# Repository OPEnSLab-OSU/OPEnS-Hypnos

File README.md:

# OpenS-Hypnos
Power Control Board for microcontroller projects, designed at OPEnS Lab OSU.

Go to [Hypnos Wiki](https://github.com/OPEnSLab-OSU/OPEnS-Lab-Home/wiki/Hypnos) for more info and build guide.

### Pinout

### Description
The OPEnS-Hypnos board is a simple, low-cost circuit board that can be attached to an Adafruit Feather M0 microcontroller and a DS3231 real-time clock breakout board to enable shutting off power to the microcontroller until a timed or sensed event wakes it up.
In the early time of development, the Feather needs to be shut down completely due to the inefficient  deep sleep firmware.
A circuit was designed to keep the state of the system, and a real-time clock can change the state and wake everything back up.
After Adafruit released new firmware for Feather M0 that allows microamp sleep current, complete shutdown of the Feather seem unnecessary.
However, during deep sleep, the 3v3 volt regulator is still providing power to other peripherals. 
MOSFET circuitry is introduced in HYPNOS to cut down power to peripherals. Additional RTC and microSD for accurate timekeeping and data logging.

* `Hypnos V2.x` Power + RTC + microSD with FeatherWing footprint. Allow control on 3.3V and VUSB rail. Using MOSFET circuit and Feather deep sleep
* `Hypnos V3.x` Upgraded from regular Hypnos. Can control one more rail of higher voltage (9-24V) at max 2.0 A continuous
* `Hypnos V3.3.lbr` Eagle library that has all of the components the Hypnos contains such as the push button, MOSFET footprints, Feather pinout, etc. 

### Specification
* Controlled 3v3 Rail (0.4 A continuous) and 5V Rail (0.5 A continuous from USB)
* [RTC DS3231](https://datasheets.maximintegrated.com/en/ds/DS3231.pdf) with TCXO
* Back up power CR1220 for RTC
* Micro SD slot

### Pinout for Feather M0
* RTC INTerrupt pin: GPIO 12
* 3.3V control pin: GPIO 5
* 5V control pin: GPIO 6
* SD chip select: GPIO 11

### How to use this board
<details>
<summary>Show more</summary>

### Important ! 3v3 RAIL ! 

Any I2C device behind [Adafruit I2C Multiplexer](https://www.adafruit.com/product/2717) does not need to be powered. We have tested the system with the Multiplexer turn off without the I2C line hanging.

Remember to power the 3.3Rail before initializing/communicating with uSD card, RTC, and I2C devices.

### Which rail to which?

* **Feather Rail:** connects directly to your Feather. Anything connected to this rail will have their power constantly on and only turn off in **Shipment Mode**. Power Control will not work on this rail.

* **Sensor/Power Rail:** connects directly to your sensor board which you wish to turn the power on/off. The 5VUSB pin and 3V pin are controlled within the rail. Digital and Analog pins on this rail connect directly to the Feather. Extra 3V|5V with LEDs are for an external plug for prototyping.

### To control the power rails:

* **3v3 rail**: Set `PIN 5` of the Feather to **LOW** for closed circuit (conduct), otherwise, the pin is pulled HIGH for open circuit (not conduct).

* **5V rail**: Set `PIN 6` to **HIGH** for closed circuit (conduct), the PIN is pulled LOW for open circuit

* **+V rail**: This pin shares control with the 5V rail. Set `PIN 6` to **HIGH** for closed circuit (conduct), the PIN is pulled LOW for open circuit

**SD card:** Chip Select `PIN 11`, **required** 3.3Rail power, normal SPI communication

**RTC DS3231:** INT-errupt `PIN 12`, **required** 3.3Rail power, I2C pull up attached to 3.3Rail

**Note:** If you need a GPIO pin **AND** you are not using one of the 3V or 5V rails, you are able to free the GPIO pin for use by cutting the trace of the rail that is not used. 

### Shipment Mode
Short the `GND` and `EN` will turn off the 3.3V regulator temporarily. The male header + Jumper cap is a great combination. Once the jumper cap is removed, the Feather will boot up normally and resume operation.

</details>

### Note
* 5Vrail can go up to 1.2A if external 5V is connected directly to **Feather USB pin**
* The LEDs are low power (rated at 2mA instead of 20mA)
* I2C line pull up is attached to 3VRail

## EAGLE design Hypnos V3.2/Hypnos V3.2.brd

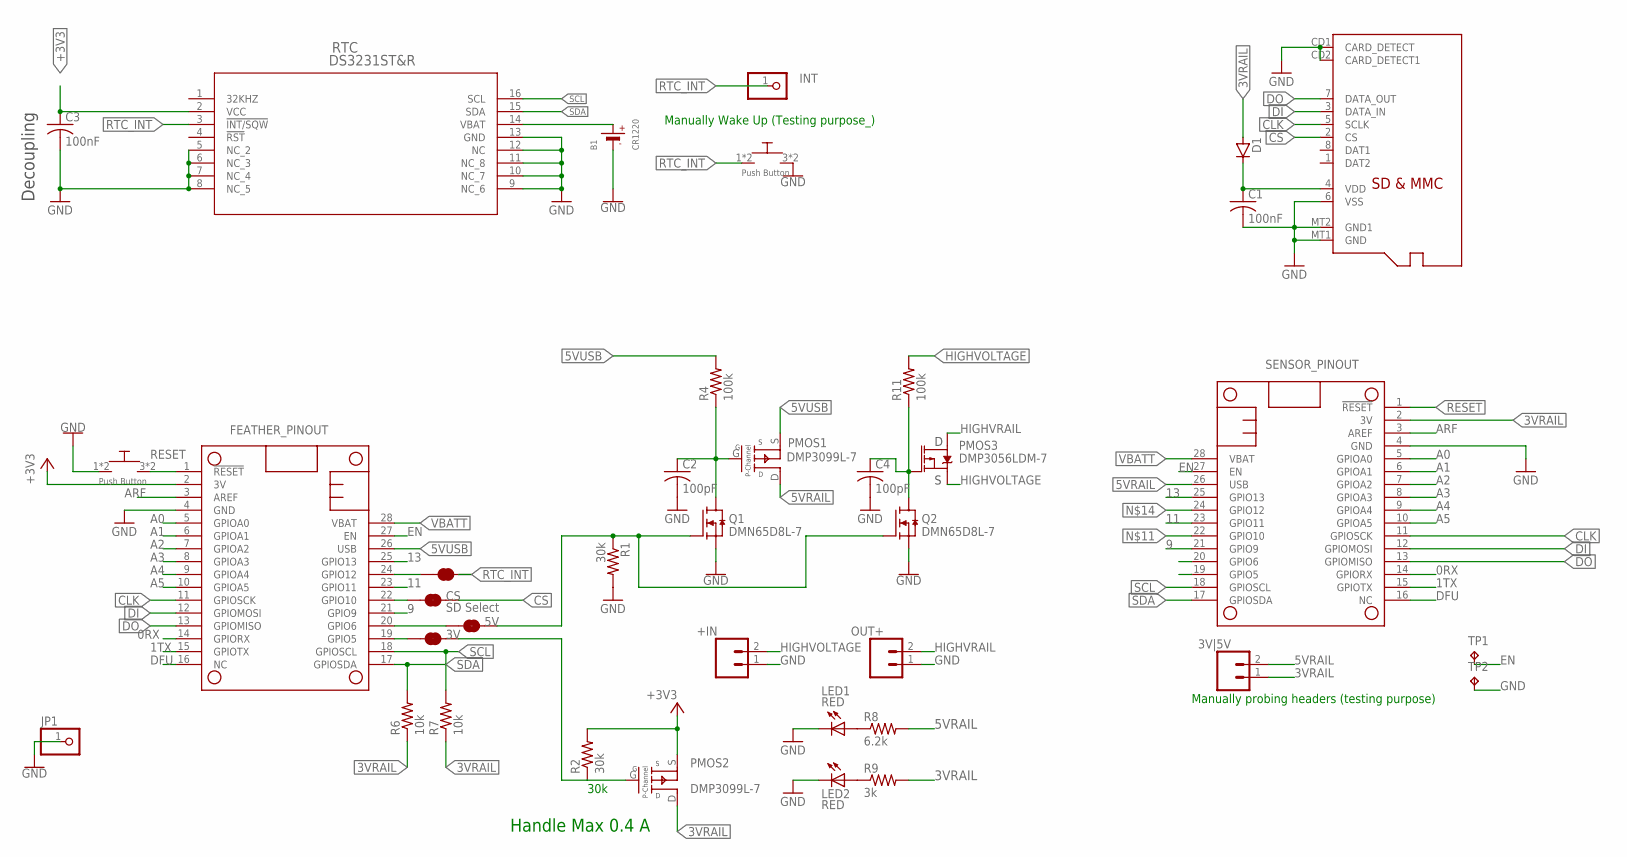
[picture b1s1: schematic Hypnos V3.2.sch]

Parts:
3V, 5V: JUMPER-SMT_2_NC_TRACE_SILK; SMT-JUMPER_2_NC_TRACE_SILK
3V|5V: CONN_021X02_NO_SILK; 1X02_NO_SILK
+IN: HIGHV-IN; 1X02_NO_SILK
B1: CR1220
C1, C3: 100nF; C1206
C2, C4: 100pF; C0805
CS: SD Select; SMT-JUMPER_2_NC_TRACE_SILK
D1: D-SOD123; SOD123
FEATHERWING: SENSOR_PINOUT; FEATHERWING
INT: PINHD-1X1CB; 1X01-CLEANBIG
JP1: PINHD-1X1CB; 1X01-CLEANBIG
LED1, LED2: RED; CHIPLED_0805
MICROSD: MICROSD
MS2: FEATHER_PINOUT; FEATHERWING
OUT+: HIGHV-OUT; 1X02_NO_SILK
PMOS1, PMOS2: DMP3099L-7; SOT-23-3
PMOS3: DMP3056LDM-7; SOT23-6
Q1, Q2: DMN65D8L-7; SOT23-S
R1, R2: 30k; RES_1206
R4, R11: 100k; RES_1206
R6, R7: 10k; RES_1206
R8: 6.2k; RES_1206
R9: 3k; RES_1206
RTC: DS3231ST&R; 21-0042B_16
RTC_INT: JUMPER-SMT_2_NC_TRACE_SILK; SMT-JUMPER_2_NC_TRACE_SILK
TP1, TP2: TPTP16R; TP16R
U$1, U$2: PUSH_BUTTON; PUSHBUTTON_SMD

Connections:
0RX: FEATHERWING.14 (GPIORX), MS2.14 (GPIORX)
1TX: FEATHERWING.15 (GPIOTX), MS2.15 (GPIOTX)
3VRAIL: 3V|5V.1, D1.2 (A), FEATHERWING.2 (3V), PMOS2.D, R6.1, R7.1, R9.2
5VRAIL: 3V|5V.2, FEATHERWING.26 (USB), PMOS1.D, R8.2
5VUSB: MS2.26 (USB), PMOS1.S, R4.2
9: FEATHERWING.21 (GPIO9), MS2.21 (GPIO9)
11: FEATHERWING.23 (GPIO11), MS2.23 (GPIO11)
13: FEATHERWING.25 (GPIO13), MS2.25 (GPIO13)
+3V3: C3.1, MS2.2 (3V), PMOS2.S, R2.2, RTC.2 (VCC)
A0: FEATHERWING.5 (GPIOA0), MS2.5 (GPIOA0)
A1: FEATHERWING.6 (GPIOA1), MS2.6 (GPIOA1)
A2: FEATHERWING.7 (GPIOA2), MS2.7 (GPIOA2)
A3: FEATHERWING.8 (GPIOA3), MS2.8 (GPIOA3)
A4: FEATHERWING.9 (GPIOA4), MS2.9 (GPIOA4)
A5: FEATHERWING.10 (GPIOA5), MS2.10 (GPIOA5)
ARF: FEATHERWING.3 (AREF), MS2.3 (AREF)
CLK: FEATHERWING.11 (GPIOSCK), MICROSD.5 (SCLK), MS2.11 (GPIOSCK)
CS: CS.2, MICROSD.2 (CS)
DFU: FEATHERWING.16 (NC), MS2.16 (NC)
DI: FEATHERWING.12 (GPIOMOSI), MICROSD.3 (DATA_IN), MS2.12 (GPIOMOSI)
DO: FEATHERWING.13 (GPIOMISO), MICROSD.7 (DATA_OUT), MS2.13 (GPIOMISO)
EN: FEATHERWING.27 (EN), MS2.27 (EN), TP1.TP
GND: +IN.1, B1.-, C1.2, C2.2, C3.2, C4.2, FEATHERWING.4 (GND), JP1.1, LED1.C, LED2.C, MICROSD.6 (VSS), MICROSD.CD1 (CARD_DETECT), MICROSD.CD2 (CARD_DETECT1), MICROSD.MT1 (GND), MICROSD.MT2 (GND1), MS2.4 (GND), OUT+.1, Q1.2 (S), Q2.2 (S), R1.2, RTC.5 (NC_2), RTC.6 (NC_3), RTC.7 (NC_4), RTC.8 (NC_5), RTC.9 (NC_6), RTC.10 (NC_7), RTC.11 (NC_8), RTC.12 (NC), RTC.13 (GND), TP2.TP, U$1.1, U$1.2, U$2.3, U$2.4
HIGHVOLTAGE: +IN.2, PMOS3.4 (S), R11.2
HIGHVRAIL: OUT+.2, PMOS3.1 (D), PMOS3.2 (D), PMOS3.5 (D), PMOS3.6 (D)
unnamed: 5V.1, MS2.20 (GPIO6)
unnamed: B1.+$1 (+), RTC.14 (VBAT)
unnamed: 3V.1, MS2.19 (GPIO5)
unnamed: 5V.2, Q1.1 (G), Q2.1 (G), R1.1
unnamed: 3V.2, PMOS2.G, R2.1
unnamed: C2.1, PMOS1.G, Q1.3 (D), R4.1
unnamed: CS.1, FEATHERWING.22 (GPIO10), MS2.22 (GPIO10)
unnamed: LED1.A, R8.1
unnamed: LED2.A, R9.1
unnamed: FEATHERWING.24 (GPIO12), MS2.24 (GPIO12), RTC_INT.1
unnamed: C4.1, PMOS3.3 (G), Q2.3 (D), R11.1
RESET: FEATHERWING.1 (!RESET), MS2.1 (!RESET), U$1.3, U$1.4
RTC_INT: INT.1, RTC.3 (!INT/SQW), RTC_INT.2, U$2.1, U$2.2
SCL: FEATHERWING.18 (GPIOSCL), MS2.18 (GPIOSCL), R7.2, RTC.16 (SCL)
SDA: FEATHERWING.17 (GPIOSDA), MS2.17 (GPIOSDA), R6.2, RTC.15 (SDA)
VBATT: FEATHERWING.28 (VBAT), MS2.28 (VBAT)
VDD: C1.1, D1.1 (C), MICROSD.4 (VDD)

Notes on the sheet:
Decoupling
Manually Wake Up (Testing purpose_)
Manually probing headers (testing purpose)
30k
Handle Max 0.4 A

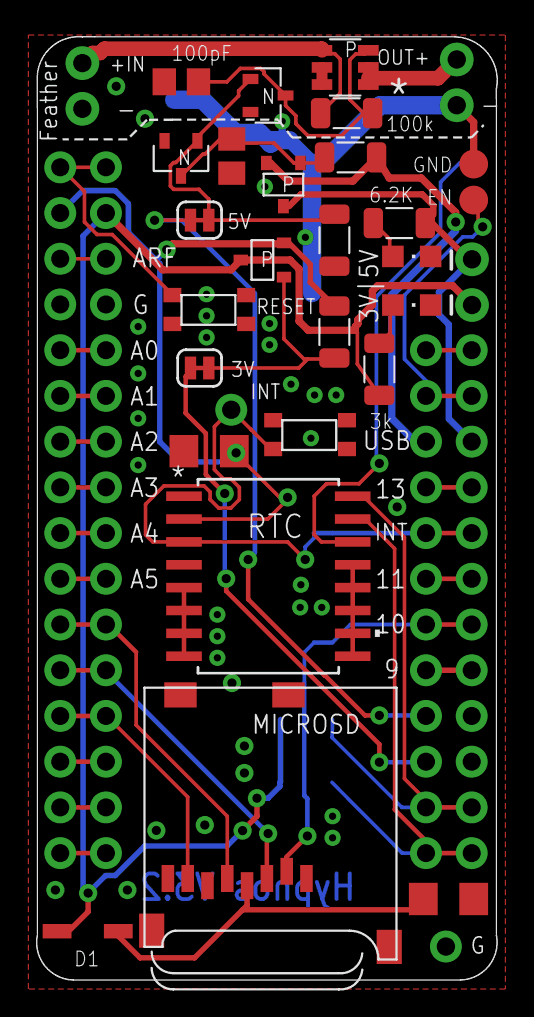
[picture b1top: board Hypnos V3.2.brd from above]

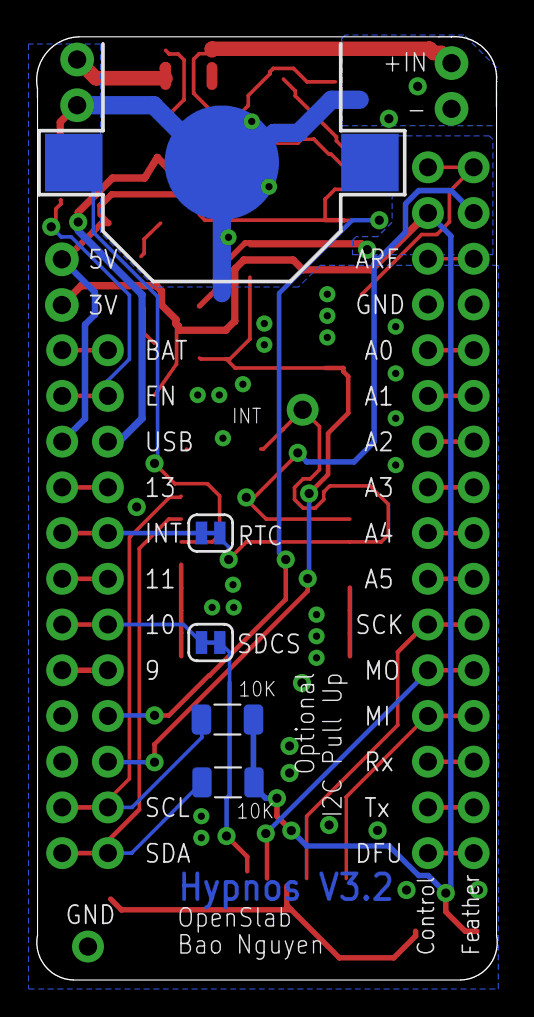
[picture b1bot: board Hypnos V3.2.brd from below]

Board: 2 copper layers, 25.6 x 52.4 mm, 38 parts (6 on the bottom side), 42 nets.

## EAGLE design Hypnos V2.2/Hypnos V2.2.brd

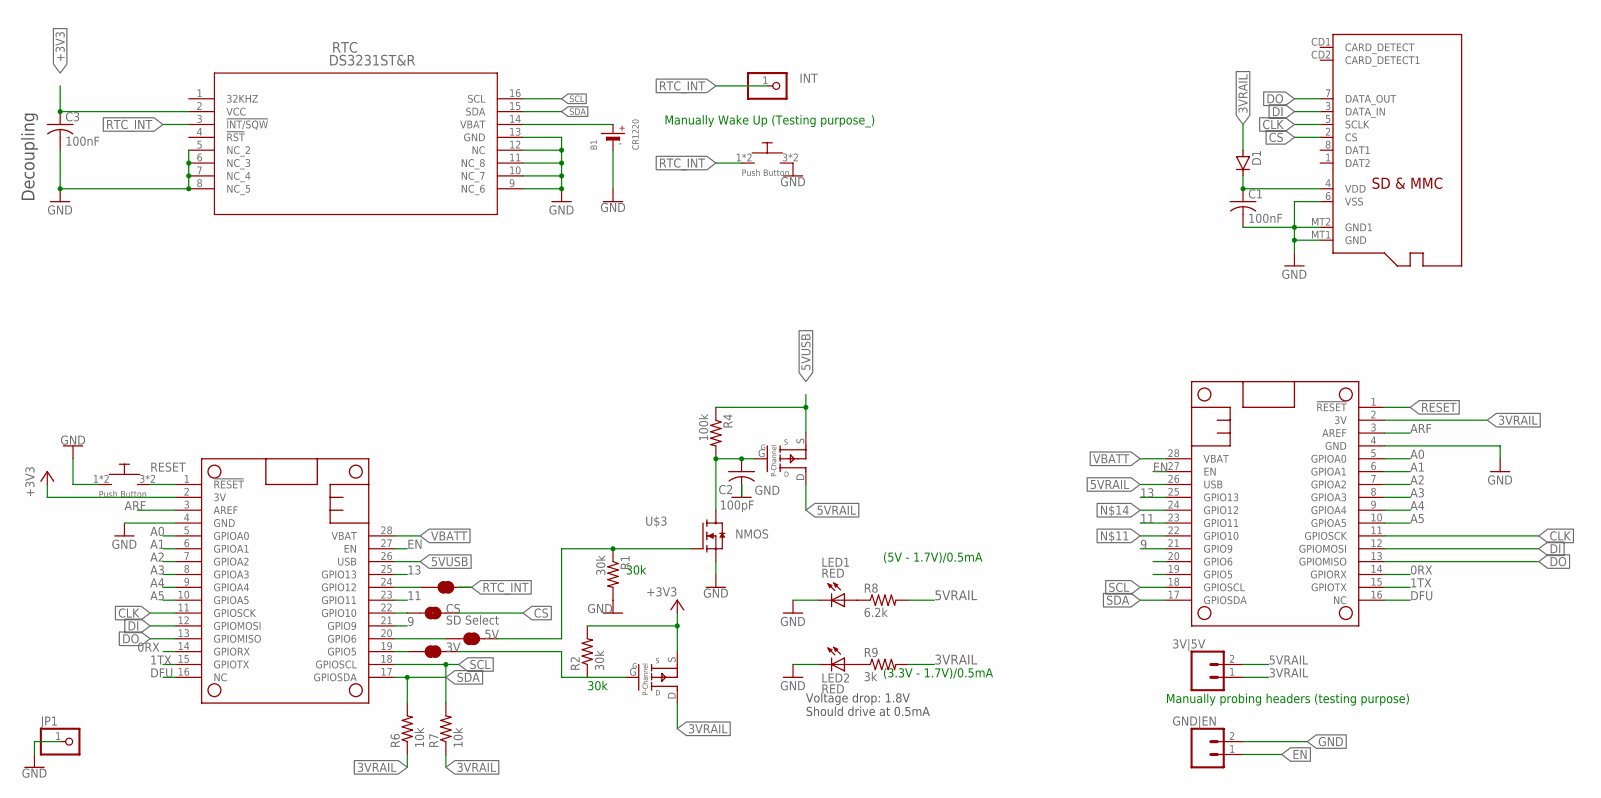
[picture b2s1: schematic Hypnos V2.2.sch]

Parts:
3V, 5V: JUMPER-SMT_2_NC_TRACE_SILK; SMT-JUMPER_2_NC_TRACE_SILK
3V|5V: CONN_021X02_NO_SILK; 1X02_NO_SILK
B1: CR1220
C1, C3: 100nF; C1206
C2: 100pF; C0805
CS: SD Select; SMT-JUMPER_2_NC_TRACE_SILK
D1: D-SOD123; SOD123
GND|EN: CONN_021X02_NO_SILK; 1X02_NO_SILK
INT: PINHD-1X1CB; 1X01-CLEANBIG
JP1: PINHD-1X1CB; 1X01-CLEANBIG
LED1, LED2: RED; CHIPLED_0805
MICROSD: MICROSD
MS1, MS2: FEATHERWING
PMOS1, PMOS2: SSM3J3228R; SOT-23-3
R1, R2: 30k; RES_1206
R4: 100k; RES_1206
R6, R7: 10k; RES_1206
R8: 6.2k; RES_1206
R9: 3k; RES_1206
RTC: DS3231ST&R; 21-0042B_16
RTC_INT: JUMPER-SMT_2_NC_TRACE_SILK; SMT-JUMPER_2_NC_TRACE_SILK
U$1, U$2: PUSH_BUTTON; PUSHBUTTON_SMD
U$3: NMOS; SOT23-S

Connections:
0RX: MS1.14 (GPIORX), MS2.14 (GPIORX)
1TX: MS1.15 (GPIOTX), MS2.15 (GPIOTX)
3VRAIL: 3V|5V.1, D1.2 (A), MS1.2 (3V), PMOS2.D, R6.1, R7.1, R9.2
5V: 3V.2, PMOS2.G, R2.1
5VRAIL: 3V|5V.2, MS1.26 (USB), PMOS1.D, R8.2
5VUSB: MS2.26 (USB), PMOS1.S, R4.1
9: MS1.21 (GPIO9), MS2.21 (GPIO9)
11: MS1.23 (GPIO11), MS2.23 (GPIO11)
13: MS1.25 (GPIO13), MS2.25 (GPIO13)
+3V3: C3.1, MS2.2 (3V), PMOS2.S, R2.2, RTC.2 (VCC)
A0: MS1.5 (GPIOA0), MS2.5 (GPIOA0)
A1: MS1.6 (GPIOA1), MS2.6 (GPIOA1)
A2: MS1.7 (GPIOA2), MS2.7 (GPIOA2)
A3: MS1.8 (GPIOA3), MS2.8 (GPIOA3)
A4: MS1.9 (GPIOA4), MS2.9 (GPIOA4)
A5: MS1.10 (GPIOA5), MS2.10 (GPIOA5)
ARF: MS1.3 (AREF), MS2.3 (AREF)
CLK: MICROSD.5 (SCLK), MS1.11 (GPIOSCK), MS2.11 (GPIOSCK)
CS: CS.2, MICROSD.2 (CS)
DFU: MS1.16 (NC), MS2.16 (NC)
DI: MICROSD.3 (DATA_IN), MS1.12 (GPIOMOSI), MS2.12 (GPIOMOSI)
DO: MICROSD.7 (DATA_OUT), MS1.13 (GPIOMISO), MS2.13 (GPIOMISO)
EN: GND|EN.1, MS1.27 (EN), MS2.27 (EN)
GND: B1.-, C1.2, C2.2, C3.2, GND|EN.2, JP1.1, LED1.C, LED2.C, MICROSD.6 (VSS), MICROSD.MT1 (GND), MICROSD.MT2 (GND1), MS1.4 (GND), MS2.4 (GND), R1.2, RTC.5 (NC_2), RTC.6 (NC_3), RTC.7 (NC_4), RTC.8 (NC_5), RTC.9 (NC_6), RTC.10 (NC_7), RTC.11 (NC_8), RTC.12 (NC), RTC.13 (GND), U$1.1, U$1.2, U$2.3, U$2.4, U$3.2 (S)
unnamed: 5V.1, MS2.20 (GPIO6)
unnamed: B1.+$1 (+), RTC.14 (VBAT)
unnamed: 3V.1, MS2.19 (GPIO5)
unnamed: 5V.2, R1.1, U$3.1 (G)
unnamed: C2.1, PMOS1.G, R4.2, U$3.3 (D)
unnamed: CS.1, MS1.22 (GPIO10), MS2.22 (GPIO10)
unnamed: LED1.A, R8.1
unnamed: LED2.A, R9.1
unnamed: MS1.24 (GPIO12), MS2.24 (GPIO12), RTC_INT.1
RESET: MS1.1 (!RESET), MS2.1 (!RESET), U$1.3, U$1.4
RTC_INT: INT.1, RTC.3 (!INT/SQW), RTC_INT.2, U$2.1, U$2.2
SCL: MS1.18 (GPIOSCL), MS2.18 (GPIOSCL), R7.2, RTC.16 (SCL)
SDA: MS1.17 (GPIOSDA), MS2.17 (GPIOSDA), R6.2, RTC.15 (SDA)
VBATT: MS1.28 (VBAT), MS2.28 (VBAT)
VDD: C1.1, D1.1 (C), MICROSD.4 (VDD)

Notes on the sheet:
Decoupling
Manually Wake Up (Testing purpose_)
Manually probing headers (testing purpose)
30k
Voltage drop: 1.8V Should drive at 0.5mA
(5V - 1.7V)/0.5mA
(3.3V - 1.7V)/0.5mA

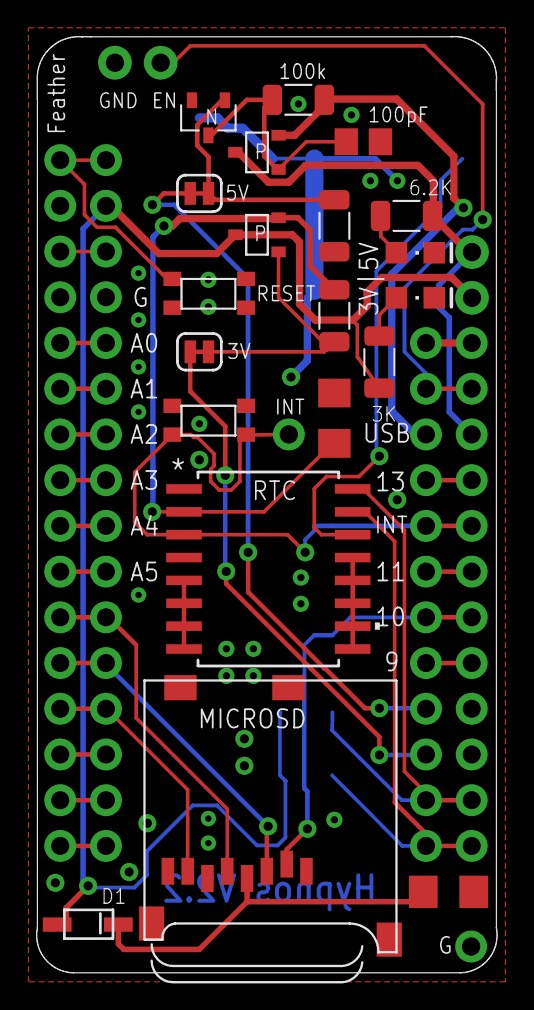
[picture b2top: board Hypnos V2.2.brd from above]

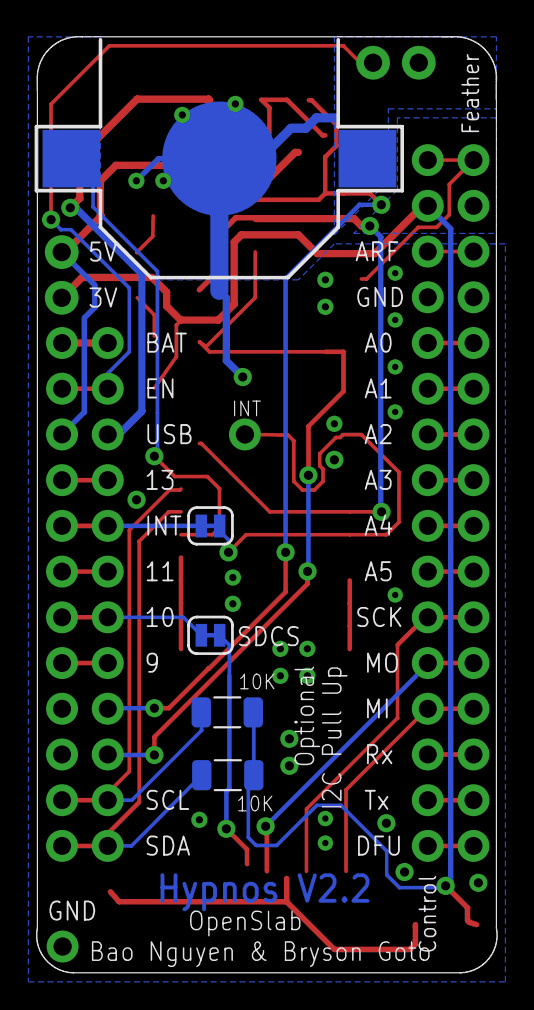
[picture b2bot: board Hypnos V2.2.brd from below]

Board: 2 copper layers, 25.6 x 52.0 mm, 31 parts (6 on the bottom side), 39 nets.

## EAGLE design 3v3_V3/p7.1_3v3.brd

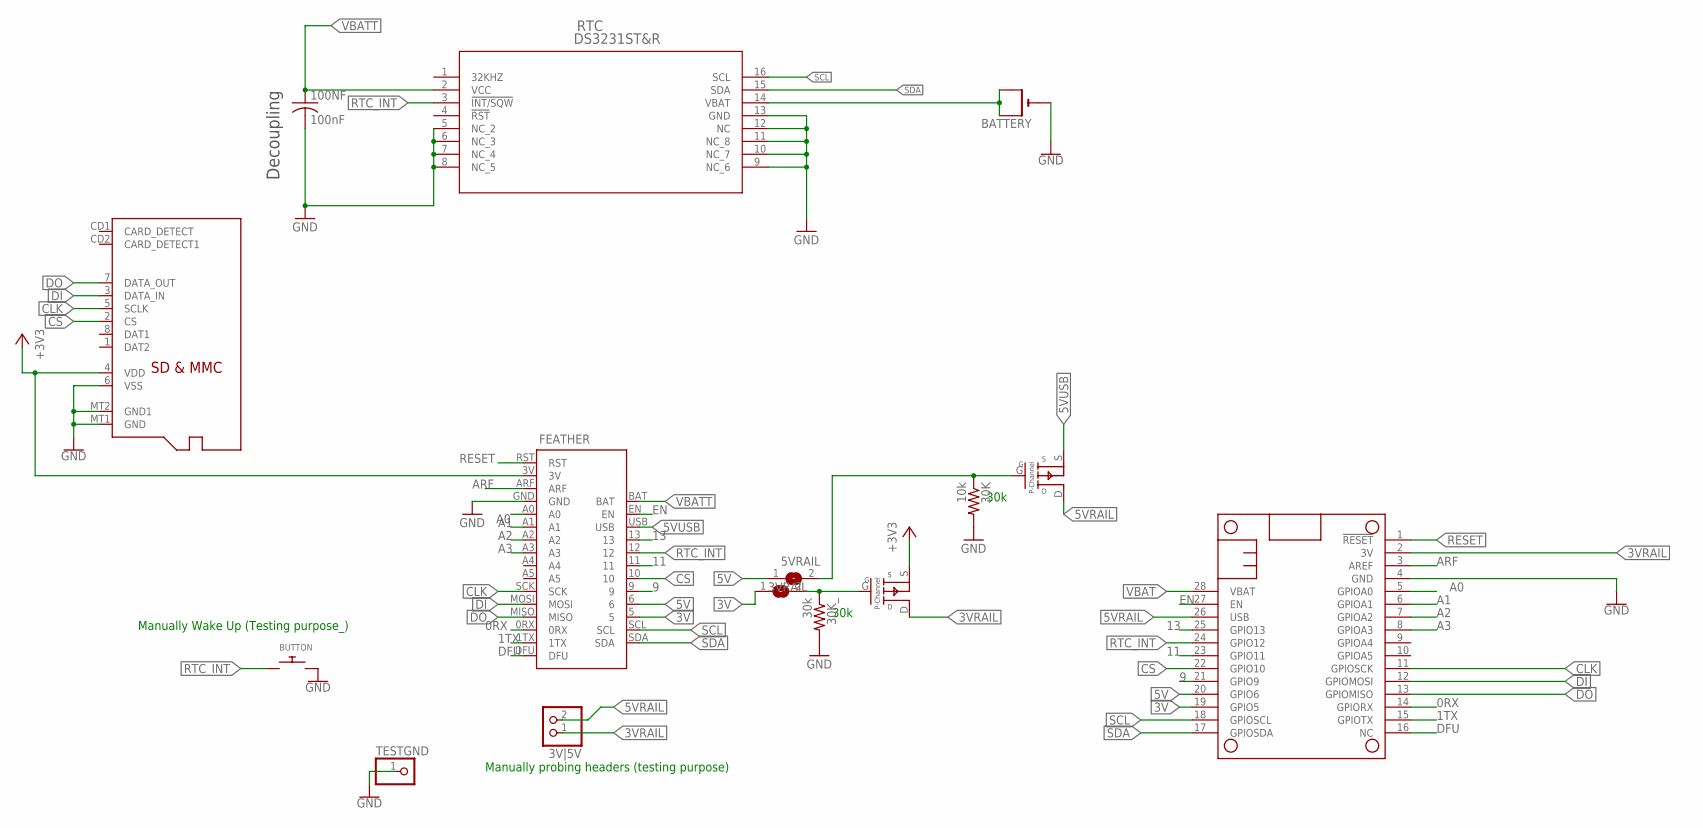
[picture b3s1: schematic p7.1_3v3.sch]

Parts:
3VRAIL, 5VRAIL: SJ
3V|5V: PINHD-1X2; 1X02
30K: 10k; R1206
30K_: 30k; R1206
100NF: 100nF; C1206
BATTERY: CR1220SMT; CR1220-SMD
BUTTON: SWITCH_PUSHBUTTONSOFTTOUCHSMD_SJ; PUSHBUTTON_SMD_SJ
FEATHER: BLUEFRUIT_M0; BLUEFRUIT_MO
MICROSD: MICROSD
MS1: FEATHERWING
PMOS: SSM3J3228R; SOT-23-3
PMOS_: SSM3J3228R; SOT-23-3
RTC: DS3231ST&R; 21-0042B_16
TESTGND: PINHD-1X1; 1X01

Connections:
0RX: FEATHER.0RX, MS1.14 (GPIORX)
1TX: FEATHER.1TX, MS1.15 (GPIOTX)
3V: 3VRAIL.1, FEATHER.5, MS1.19 (GPIO5)
3VRAIL: 3V|5V.1, MS1.2 (3V), PMOS.D
5V: 5VRAIL.1, FEATHER.6, MS1.20 (GPIO6)
5VRAIL: 3V|5V.2, 5VRAIL.2, 30K.1, MS1.26 (USB), PMOS_.D, PMOS_.G
5VUSB: FEATHER.USB, PMOS_.S
9: FEATHER.9, MS1.21 (GPIO9)
11: FEATHER.11, MS1.23 (GPIO11)
13: FEATHER.13, MS1.25 (GPIO13)
+3V3: FEATHER.3V, MICROSD.4 (VDD), PMOS.S
A0: FEATHER.A0, MS1.5 (GPIOA0)
A1: FEATHER.A1, MS1.6 (GPIOA1)
A2: FEATHER.A2, MS1.7 (GPIOA2)
A3: FEATHER.A3, MS1.8 (GPIOA3)
ARF: FEATHER.ARF, MS1.3 (AREF)
CLK: FEATHER.SCK, MICROSD.5 (SCLK), MS1.11 (GPIOSCK)
CS: FEATHER.10, MICROSD.2 (CS), MS1.22 (GPIO10)
DFU: FEATHER.DFU, MS1.16 (NC)
DI: FEATHER.MOSI, MICROSD.3 (DATA_IN), MS1.12 (GPIOMOSI)
DO: FEATHER.MISO, MICROSD.7 (DATA_OUT), MS1.13 (GPIOMISO)
EN: FEATHER.EN, MS1.27 (EN)
GND: 30K.2, 30K_.2, 100NF.2, BATTERY.-, BUTTON.P$2, FEATHER.GND, MICROSD.6 (VSS), MICROSD.MT1 (GND), MICROSD.MT2 (GND1), MS1.4 (GND), RTC.5 (NC_2), RTC.6 (NC_3), RTC.7 (NC_4), RTC.8 (NC_5), RTC.9 (NC_6), RTC.10 (NC_7), RTC.11 (NC_8), RTC.12 (NC), RTC.13 (GND), TESTGND.1
unnamed: BATTERY.+$1 (+), BATTERY.+$2 (+1), RTC.14 (VBAT)
OUTPUT3V3: 3VRAIL.2, 30K_.1, PMOS.G
RESET: FEATHER.RST, MS1.1 (!RESET)
RTC_INT: BUTTON.P$1, FEATHER.12, MS1.24 (GPIO12), RTC.3 (!INT/SQW)
SCL: FEATHER.SCL, MS1.18 (GPIOSCL), RTC.16 (SCL)
SDA: FEATHER.SDA, MS1.17 (GPIOSDA), RTC.15 (SDA)
VBAT: MS1.28 (VBAT)
VBATT: 100NF.1, FEATHER.BAT, RTC.2 (VCC)

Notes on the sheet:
Decoupling
Manually Wake Up (Testing purpose_)
Manually probing headers (testing purpose)
30k

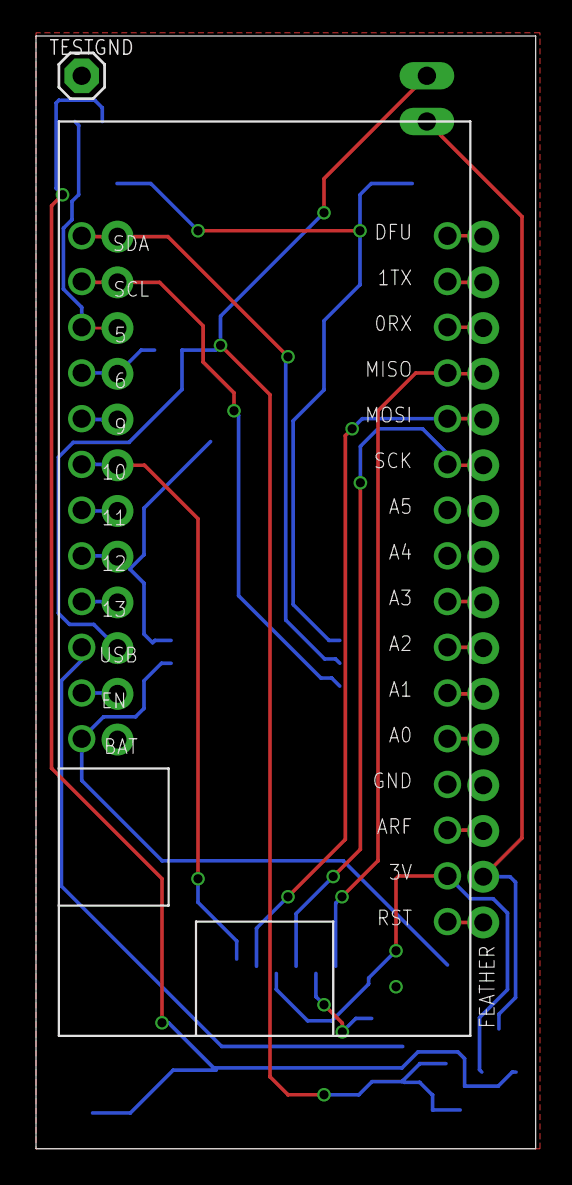
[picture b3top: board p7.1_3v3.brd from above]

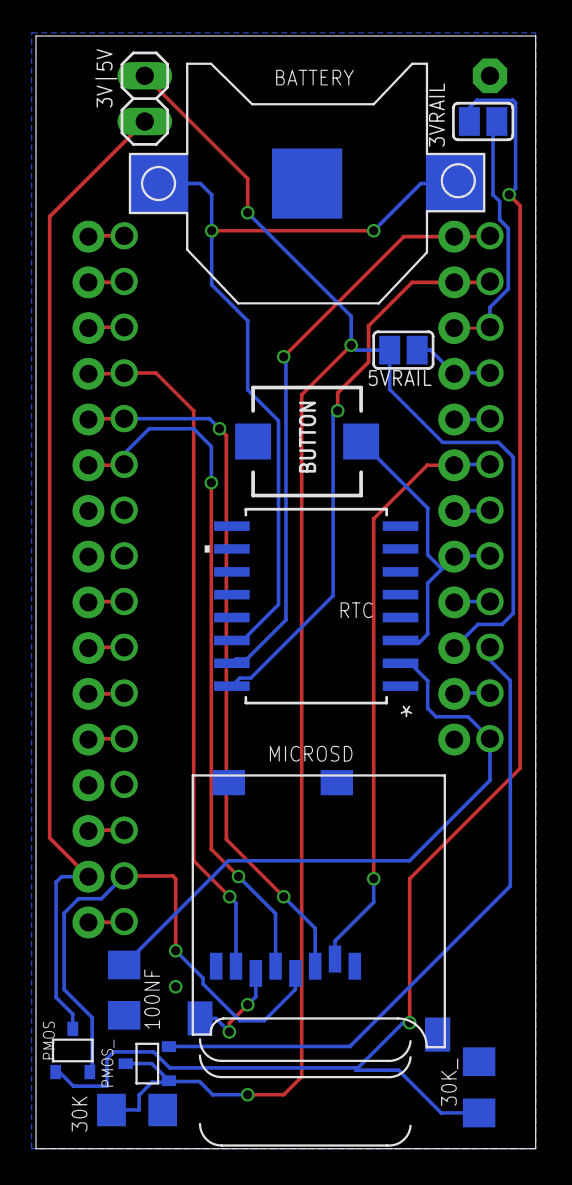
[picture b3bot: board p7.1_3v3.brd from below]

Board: 2 copper layers, 27.8 x 61.8 mm, 15 parts (12 on the bottom side), 30 nets.

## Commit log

2019-01-03 Changed names to match first release.
    This is now version 1.0.0 of OPEnS-Power, and was previously named Power7.1
2019-04-15 Add files via upload
    Added 3v3 Board
2019-05-10 Fixed ground issue
    GND pin
2019-08-30 Final update for 3.3V prototype
2019-08-30 Updated Bill of Material
2019-08-30 Archiving older versions
    Short info is included in Reason for archiving.txt
2019-08-30 Added 12V version with RTC
    This board is currently tested on the eDNA
    Added eDNA eagle lib
    Archived older versions
2019-08-31 Added 3 Volt V3 images
2019-08-31 Add 12v 7.2 images
2019-09-04 Added readme for 12V 7.2
2019-09-04 Update BOM OPEnS Power 7.2.xlsx
    Add cost and remove overlap listing
2019-10-03 Remove 12V OpenSpower
    Remove 12V version to other repo for easier version control
2019-10-03 Testing for Version V2
    Update from Version 1:
    * 2 LEDs with current limiting resistors
    * RTC is now powered from 3V3 instead of Vbat (using power from Vbat turns on Feather Battery Charger LED)
    * Pull up resistor for SD chip select just like adalogger
    * Rounded PCB corner
    * Move the reset button to the middle of the board - mechanically more stable
2019-10-08 Schematic Change for Hypnos V2
    Update Hypnos V2
    * Change from BJT to Logic MOSFET. Using BJT require current limiting resistor and also involve more calculation.
    * Remove R5 to simplify the circuit
    * Increase trace width for all power rail
    * Change resistors footprint to get more space and better indication for solder orientation
    Update eDNA.lbr
2019-10-15 Update Bill of Materials - Hypnos V2.xlsx
    Update the right part for 100k ohm resistor
2019-10-22 N-Mos Bug FIx
    Wrong footprint layout - Drain and Source was switched
2019-11-01 Hypnos V3 Beta
    Hypnos V3 PCBs design is finalized. Sent out for fabrication for further testing.
2019-11-01 Update README.md
    Add Hypnos V3 info
2019-11-26 Update Bill of Material Hypnos V2
    Correction to 100pF Part ID Digikey
2020-01-27 Added Diode
    Hardware fix for uSD card current leak. Added diode with low current leakage to prevent current from SPI pins going back to 3VRAIL.
2020-01-27 Update Bill of Materials - Hypnos V2.xlsx
    Remove 82k resistor. New schematic does not use the same part.
2020-01-28 Hypnos V3 hardware fix
    Added diode to Hypnos V3 to minimize leaking current from uSD card to 3VRAIL.
    Add pdf for schematic Hypnos V2 + Hypnos V3
    Updated bill of material to Hypnos V3
2020-03-24 I2C line connected to 3.3Rail
    Remoce I2C line from 3.3Rail reduce power going back to sersor when they are turned off.
2020-03-31 Add files via upload
    I2C line connected to 3.3Rail
2020-03-31 I2C line connected to 3.3Rail
2020-04-09 Renamed for convention
2020-04-10 Update 3V trace for Hypnos V3
    Route missing trace for V3
    Add bStop layer for V2
    Clean up some note on schematic V2 and V3
2020-04-13 Updated 3V Trace for Hypnos V3
2020-05-10 Folder prep for release
    Updated
    +Readme
    +Folder name
    +Gerber files
2020-05-24 Update BOM
2020-06-30 Remove 100pf, replace to alway connected solder pad
2020-07-03 Hypnos 2.2 and 3.2
    +Change solder bridge to always connected pad
    +Remove solder bridge for D1 diode
2020-07-03 Add another uSD part
    BOM has a new part link for uSD slot
2020-07-18 Added board + schematic PDFs
2020-08-03 Fixed equation for 10k resistor
2020-09-04 Updated Zenodo file
2020-09-04 Updated .json for Zenodo
2021-01-14 Updated Zenodo
2021-05-12 Updated documentation (BOM, components in schematics, pick-n-place file)
2021-05-12 HardwareX documentation revision
2021-05-12 Update RTC documentation
2021-07-27 Hypnos V3.3 Update
    Changed SD pin from GPIO10 to GPIO9 and removed extra capacitors from design
2021-07-28 Hypnos V3.3 Update
    Switched SD pin from pin 9 to pin 11 due to Feather pin issues, updated BOM with in-stock parts from Digikey
2021-09-24 Update HypnosV3.3_Sch.pdf
    Fixed flipped schematic
2023-01-06 Create x
2023-07-27 Added 3.2 for reference

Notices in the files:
parts and their libraries:
SparkFun-PowerSymbols: Licensing: Creative Commons ShareAlike 4.0 International - https://creativecommons.org/licenses/by-sa/4.0
microbuilder: This work is placed in the public domain, and may be freely used for commercial and non-commercial work with the following conditions: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
